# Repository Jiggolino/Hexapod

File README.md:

This project is under construction!

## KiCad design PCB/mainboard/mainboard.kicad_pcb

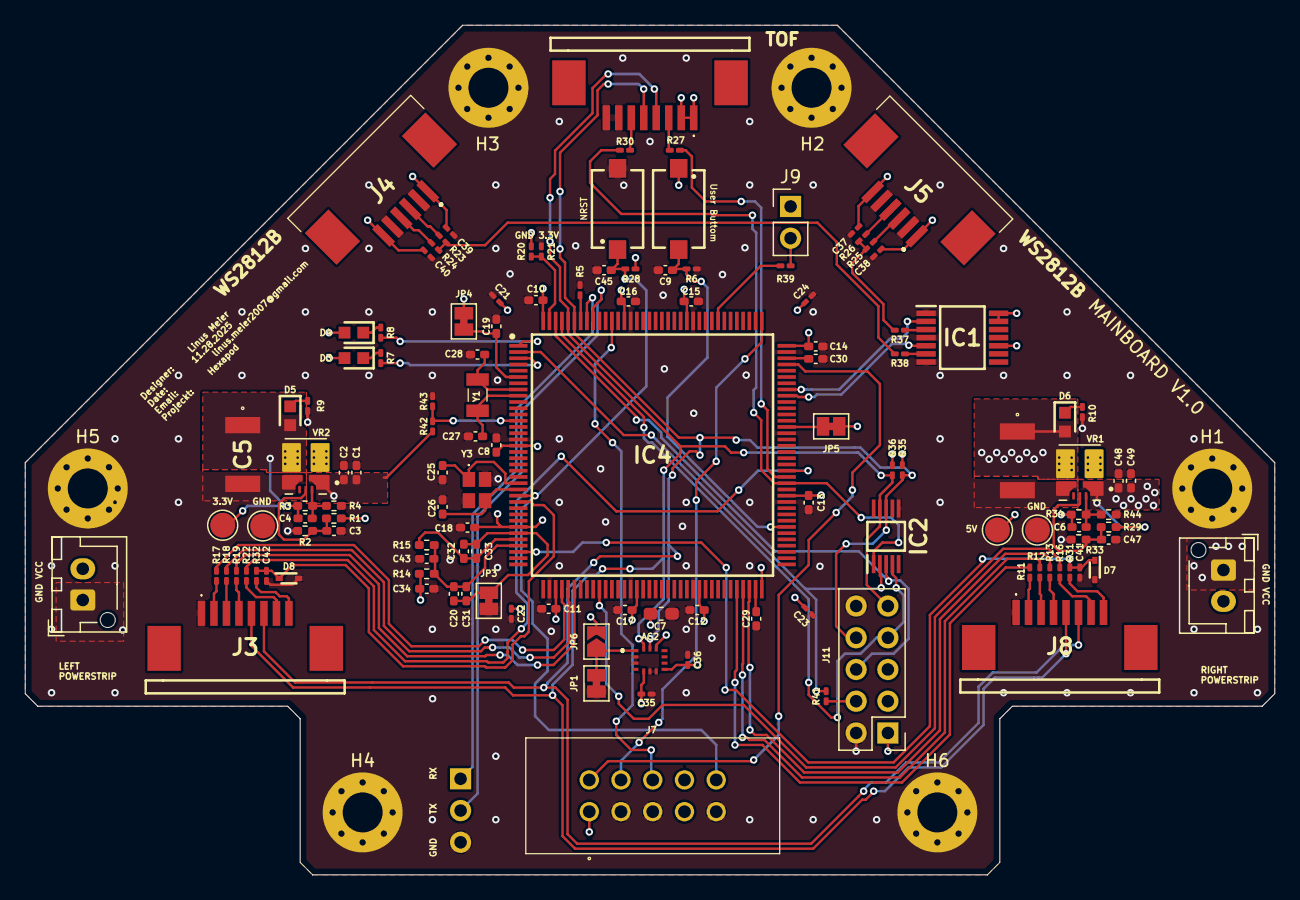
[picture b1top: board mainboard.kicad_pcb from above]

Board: 4 copper layers, 100.0 x 68.0 mm, 133 parts (1 on the bottom side), 78 nets.

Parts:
AC2: LSM6DSOTR; LSM6DS3USTR
C1, C49: 10u; C_0402_1005Metric_Pad0.74x0.62mm_HandSolder
C2, C9, C45, C48: 100n; C_0402_1005Metric_Pad0.74x0.62mm_HandSolder
C3, C47: 10n; C_0402_1005Metric_Pad0.74x0.62mm_HandSolder
C4, C6: 22p; C_0402_1005Metric_Pad0.74x0.62mm_HandSolder
C5, C46: 33u; C4532_Commercial
C7: 4.7uF; C_0603_1608Metric_Pad1.08x0.95mm_HandSolder
C8, C10, C11, C12, C13, C14, C15, C16, C17, C18, C31, C33, C34, C43: 100nF; C_0402_1005Metric_Pad0.74x0.62mm_HandSolder
C19, C20, C32: 1uF; C_0402_1005Metric_Pad0.74x0.62mm_HandSolder
C21, C22, C23, C24, C37, C38, C39, C40: 1u; C_0201_0603Metric_Pad0.64x0.40mm_HandSolder
C25, C26: 6pF; C_0402_1005Metric_Pad0.74x0.62mm_HandSolder
C27, C28: 8pF; C_0402_1005Metric_Pad0.74x0.62mm_HandSolder
C29, C30: 2.2u; C_0402_1005Metric_Pad0.74x0.62mm_HandSolder
C35, C36, C41, C42: 100n; C_0201_0603Metric_Pad0.64x0.40mm_HandSolder
D3: LED_Red; LEDC1608X70N
D4, D5, D6: LED_Geen; LEDC1608X70N
D7, D8: BZT585B3V3T-7; SODFL1608X65N
H1, H2, H3, H4, H5, H6: MountingHole_Pad; MountingHole_3.2mm_M3_Pad_Via
IC1: 74HCT125T14-13; SOP65P640X120-14N
IC2: SP4065-08ATG; SOP50P488X110-10N
IC4: STM32H743ZIT6; QFP50P2200X2200X160-144N
J1: Right Strip Power; JST_XH_B2B-XH-AM_1x02_P2.50mm_Vertical
J2: Left Strip Power; JST_XH_B2B-XH-AM_1x02_P2.50mm_Vertical
J3: Left Strip; 17352658
J4: LED Strip left; 849526
J5: LED Strip right; 849526
J6: Time Of Flight; 17352658
J7: TST-105-01-L-D; TST-105-XX-Y-D
J8: Right Strip; 17352658
J9: LED_CAM; PinHeader_1x02_P2.54mm_Vertical
J10: Uart Connector to pi5; PinSocket_1x03_P2.54mm_Vertical
J11: Conn_02x05_Counter_Clockwise; PinHeader_2x05_P2.54mm_Vertical
JP1, JP3, JP4, JP5: SolderJumper_2_Bridged; SolderJumper-2_P1.3mm_Bridged_Pad1.0x1.5mm
JP6: SolderJumper_2_Open; SolderJumper-2_P1.3mm_Open_TrianglePad1.0x1.5mm
R1, R29: 27.4k; R_0402_1005Metric_Pad0.72x0.64mm_HandSolder
R2, R33: 10k; R_0402_1005Metric_Pad0.72x0.64mm_HandSolder
R3: 220k; R_0402_1005Metric_Pad0.72x0.64mm_HandSolder
R4, R44: 30k; R_0402_1005Metric_Pad0.72x0.64mm_HandSolder
R5, R6, R20, R21, R28, R43: 10k; R_0201_0603Metric_Pad0.64x0.40mm_HandSolder
R7, R8, R9, R39: 100R; R_0201_0603Metric_Pad0.64x0.40mm_HandSolder
R10: 270R; R_0201_0603Metric_Pad0.64x0.40mm_HandSolder
R11, R12, R13, R16, R17, R18, R19, R22, R23, R24, R25, R26, R27, R30, R37, R38, R41: 47R; R_0201_0603Metric_Pad0.64x0.40mm_HandSolder
R14, R15: 0R; R_0402_1005Metric_Pad0.72x0.64mm_HandSolder
R31, R32: 10R; R_0201_0603Metric_Pad0.64x0.40mm_HandSolder
R34: 135k; R_0402_1005Metric_Pad0.72x0.64mm_HandSolder
R35, R36: 4.7k; R_0201_0603Metric_Pad0.64x0.40mm_HandSolder
R42: 100k; R_0201_0603Metric_Pad0.64x0.40mm_HandSolder
S1, S4: 434121025816
TP1, TP2, TP3, TP4: TestPoint; TestPoint_Pad_D2.0mm
VR1, VR2: TPSM863252RDXR; VREG_TPSM863252RDXR
Y1: CM7V-T1A-32.768KHZ-7PF-20PPM-TA-QC; CM7V32768TBQA020
Y3: ECS-250-8-36CKM-TR3; ECS250836CKMTR3

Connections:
+3V3: AC2.5 (VDDIO), AC2.8 (VDD), AC2.12 (CS), C4.1, C5.1, C7.1, C8.1, C10.1, C11.1, C12.1, C13.1, C14.1, C15.1, C16.1, C17.1, C18.1, C21.1, C22.1, C23.1, C24.1, C34.1, C35.1, C36.1, D3.2 (A), D4.2 (A), D5.2 (A), IC4.17 (VDD_1), IC4.30 (VDD_2), IC4.39 (VDD_3), IC4.52 (VDD_4), IC4.62 (VDD_5), IC4.72 (VDD_6), IC4.84 (VDD_7), IC4.108 (VDD_8), IC4.121 (VDD_9), IC4.131 (VDD_10), IC4.144 (VDD_11), J6.1, J6.2, J7.1, J9.1, J11.1, JP4.2 (B), JP5.1 (A), JP6.2 (B), R3.1, R14.1, R20.2, R28.2, R35.1, R36.1, S1.1 (COM), TP3.1, VR2.3 (VOUT)
+5V: C6.1, C37.1, C38.1, C39.1, C40.1, C46.1, D6.2 (A), IC1.10 (3~OE), IC1.13 (4~OE), IC1.14 (VCC), J4.1, J4.6, J5.1, J5.6, J11.5, R34.1, TP1.1, VR1.3 (VOUT)
Battery Voltage: IC4.13 (PF3), R42.1, R43.2
Boot0: IC4.138 (BOOT0), R5.2
DIN Board 1: R23.2, R24.2, R38.1
DIN Board 2: R25.2, R26.2, R37.1
DIN WS2812B Board 1 3.3V: IC1.5 (2A), IC4.100 (PA8)
DIN WS2812B Board 2 3.3V: IC1.2 (1A), IC4.101 (PA9)
GND: AC2.2 (SDX), AC2.3 (SCX), AC2.6 (GND_1), AC2.7 (GND_2), C1.2, C2.2, C3.2, C5.2, C7.2, C8.2, C9.1, C10.2, C11.2, C12.2, C13.2, C14.2, C15.2, C16.2, C17.2, C18.2, C19.2, C21.2, C22.2, C23.2, C24.2, C25.1, C26.2, C27.2, C28.2, C29.2, C30.2, C34.2, C35.2, C36.2, C37.2, C38.2, C39.2, C40.2, C41.2, C42.2, C43.2, C45.1, C46.2, C47.2, C48.2, C49.2, D7.2 (A), D8.2 (A), H1.1, H2.1, H3.1, H4.1, H5.1, H6.1, IC1.1 (1~OE), IC1.4 (2~OE), IC1.7 (GND), IC2.6 (GND), IC4.16 (VSS_1), IC4.38 (VSS_2), IC4.51 (VSS_3), IC4.61 (VSS_4), IC4.83 (VSS_5), IC4.94 (VSS_6), IC4.107 (VSS_7), IC4.120 (VSS_8), IC4.130 (VSS_9), J1.1, J2.1, J3.1, J4.2, J4.5, J5.2, J5.5, J6.7, J6.8, J7.3, J7.5, J7.9, J8.1, J10.3, J11.2, J11.10, JP1.1 (A), JP3.1 (A), R2.2, R4.2, R5.1, R6.1, R9.2, R10.2, R21.2, R33.2, R43.1, R44.2, S4.2 (NO), TP2.1, TP4.1, VR1.4 (PGND), VR2.4 (PGND), Y3.2 (GND_1), Y3.4 (GND_2)
GNDA: C20.2, C31.2, C32.2, C33.2, IC4.31 (VSSA), JP3.2 (B)
GPIO 1: IC4.87 (PG2), R27.2
GPIO Expansion 1: IC2.4 (I/O_4), IC4.141 (PE0), J11.7
GPIO Expansion 2: IC2.3 (I/O_3), IC4.142 (PE1), J11.6
GPIO Expansion 3: IC2.2 (I/O_2), IC4.2 (PE3), R41.1
LED_CAM: IC4.116 (PD2), R39.2
NRST: C45.2, IC4.25 (NRST), J7.10, R28.1, S4.1 (COM)
unnamed: AC2.1 (SDO/SA0), JP1.2 (B), JP6.1 (A)
unnamed: D3.1 (K), R7.1
unnamed: D4.1 (K), R8.1
unnamed: D5.1 (K), R9.1
unnamed: D6.1 (K), R10.1
unnamed: IC1.3 (1Y), R37.2
unnamed: IC1.6 (2Y), R38.2
unnamed: J3.2, R17.1
unnamed: J3.3, R18.1
unnamed: J3.4, R19.1
unnamed: J3.7, R22.1
unnamed: J3.8, R32.1
unnamed: J4.3, R23.1
unnamed: J4.4, R24.1
unnamed: J5.3, R25.1
unnamed: J5.4, R26.1
unnamed: J6.3, R27.1
unnamed: J6.6, R30.1
unnamed: J8.2, R11.1
unnamed: J8.3, R12.1
unnamed: J8.4, R13.1
unnamed: J8.7, R16.1
unnamed: J8.8, R31.1
unnamed: J9.2, R39.1
unnamed: J11.4, R41.2
unnamed: C47.1, R29.2, R33.1, VR1.6 (EN)
unnamed: C6.2, R34.2, R44.1, VR1.7 (FB)
unnamed: C3.1, R1.2, R2.1, VR2.6 (EN)
unnamed: C4.2, R3.2, R4.1, VR2.7 (FB)
PC14-OSC32_IN: C28.1, IC4.8 (PC14-OSC32_IN), Y1.1
PC15-OSC32_OUT: C27.1, IC4.9 (PC15-OSC32_OUT), Y1.2
PDR_ON: IC4.143 (PDR_ON), R20.1, R21.1
PE2 (LED): IC4.1 (PE2), R8.2
PE4 (LED): IC4.3 (PE4), R7.2
PH0-OSC_IN: C25.2, IC4.23 (PH0-OSC_IN), Y3.1 (IN/OUT)
PH1-OSC_OUT: C26.1, IC4.24 (PH1-OSC_OUT), Y3.3 (OUT/IN)
RX: IC4.137 (PB7), J10.1
SCL: AC2.13 (SCL), IC2.8 (I/O_6), IC4.139 (PB8), J3.6, J6.5, J8.6, J11.8, R35.2
SDA: AC2.14 (SDA), IC2.9 (I/O_7), IC4.140 (PB9), J3.5, J6.4, J8.5, J11.9, R36.2
SWCLK: IC4.109 (PA14), J7.4
SWDIO: IC4.105 (PA13), J7.2
SWO: IC4.133 (PB3), J7.6
TX: IC4.136 (PB6), J10.2
User Button: C9.2, IC4.79 (PD10), R6.2, S1.2 (NO)
VBAT: C19.1, IC4.6 (VBAT), JP4.1 (A)
VCAP_1: C29.1, IC4.71 (VCAP_1)
VCAP_2: C30.1, IC4.106 (VCAP_2)
VCC: C1.1, C2.1, C48.1, C49.1, J1.2, J2.2, J11.3, R1.1, R29.1, R42.2, VR1.1 (VIN), VR2.1 (VIN)
VDD33_USB: IC4.95 (VDD33USB), JP5.2 (B)
VDDA: C20.1, C31.1, C43.1, IC4.33 (VDDA), R14.2, R15.1
VREFP: C32.1, C33.1, IC4.32 (VREF+), R15.2
XSHUT: IC2.1 (I/O_1), IC4.86 (PD15), R30.2
left_A0: IC4.42 (PA6), R19.2
left_A1: IC4.41 (PA5), R18.2
left_A2: IC4.40 (PA4), R17.2
left_ADC INPUT: C42.1, D8.1 (K), IC4.26 (PC0), R32.2
left_¬EN: IC4.88 (PG3), R22.2
right_A0: IC4.70 (PB11), R13.2
right_A1: IC4.69 (PB10), R12.2
right_A2: IC4.68 (PE15), R11.2
right_ADC INPUT: C41.1, D7.1 (K), IC4.34 (PA0), R31.2
right_¬EN: IC4.46 (PB0), R16.2

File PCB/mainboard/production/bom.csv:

Designator,Footprint,Quantity,Value,LCSC Part #
AC2,LSM6DS3USTR,1,LSM6DSOTR,
"C1, C49",0402,2,10u,
"C10, C11, C12, C13, C14, C15, C16, C17, C18, C31, C33, C34, C43, C8",0402,14,100nF,
"C19, C20, C32",0402,3,1uF,
"C2, C45, C48, C9",0402,4,100n,
"C21, C22, C23, C24, C37, C38, C39, C40",0201,8,1u,
"C25, C26",0402,2,6pF,
"C27, C28",0402,2,8pF,
"C29, C30",0402,2,2.2u,
"C3, C47",0402,2,10n,
"C35, C36, C41, C42",0201,4,100n,
"C4, C6",0402,2,22p,
"C46, C5",C4532_Commercial,2,33u,
C7,0603,1,4.7uF,
D3,LEDC1608X70N,1,LED_Red,
"D4, D5, D6",LEDC1608X70N,3,LED_Geen,
"D7, D8",SODFL1608X65N,2,BZT585B3V3T-7,
IC1,SOP65P640X120-14N,1,74HCT125T14-13,
IC2,SOP50P488X110-10N,1,SP4065-08ATG,
IC4,QFP50P2200X2200X160-144N,1,STM32H743ZIT6,
J1,JST_XH_B2B-XH-AM_1x02_P2.50mm_Vertical,1,Right Strip Power,
J10,PinSocket_1x03_P2.54mm_Vertical,1,Uart Connector to pi5,
J11,PinHeader_2x05_P2.54mm_Vertical,1,Conn_02x05_Counter_Clockwise,
J2,JST_XH_B2B-XH-AM_1x02_P2.50mm_Vertical,1,Left Strip Power,
J3,17352658,1,Left Strip,
J4,849526,1,LED Strip left,
J5,849526,1,LED Strip right,
J6,17352658,1,Time Of Flight,
J7,TST-105-XX-Y-D,1,TST-105-01-L-D,
J8,17352658,1,Right Strip,
J9,PinHeader_1x02_P2.54mm_Vertical,1,LED_CAM,
"R1, R29",0402,2,27.4k,
R10,0201,1,270R,
"R11, R12, R13, R16, R17, R18, R19, R22, R23, R24, R25, R26, R27, R30, R37, R38, R41",0201,17,47R,
"R14, R15",0402,2,0R,
"R2, R33",0402,2,10k,
"R20, R21, R28, R43, R5, R6",0201,6,10k,
R3,0402,1,220k,
"R31, R32",0201,2,10R,
R34,0402,1,135k,
"R35, R36",0201,2,4.7k,
"R39, R7, R8, R9",0201,4,100R,
"R4, R44",0402,2,30k,
R42,0201,1,100k,
"S1, S4",434121025816,2,434121025816,
"TP1, TP2, TP3, TP4",TestPoint_Pad_D2.0mm,4,TestPoint,
"VR1, VR2",VREG_TPSM863252RDXR,2,TPSM863252RDXR,
Y1,CM7V32768TBQA020,1,CM7V-T1A-32.768KHZ-7PF-20PPM-TA-QC,
Y3,ECS250836CKMTR3,1,ECS-250-8-36CKM-TR3,

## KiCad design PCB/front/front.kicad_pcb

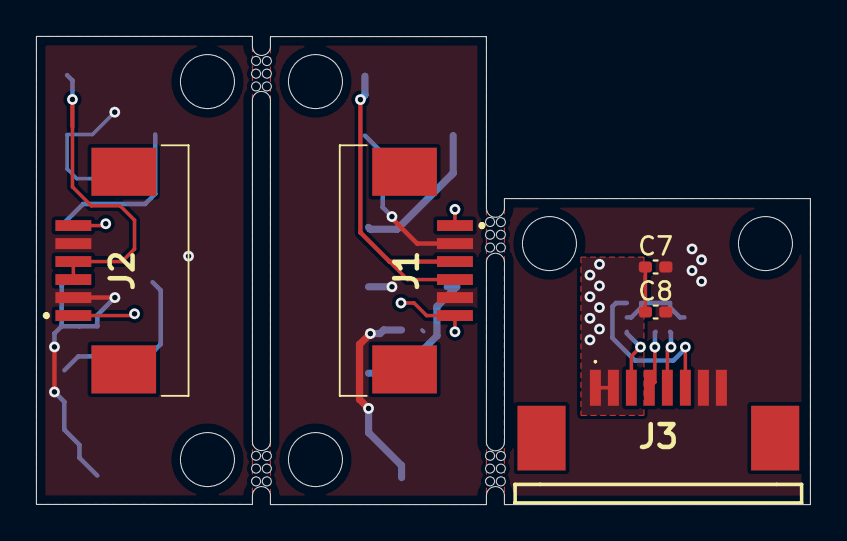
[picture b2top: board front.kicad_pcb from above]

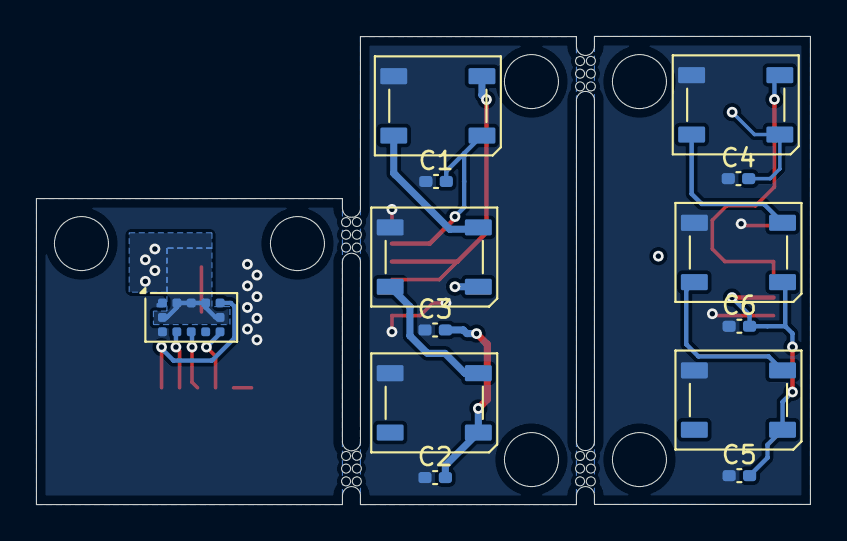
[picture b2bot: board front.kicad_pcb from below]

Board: 2 copper layers, 43.0 x 26.0 mm, 22 parts (13 on the bottom side), 16 nets.

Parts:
C1, C2, C3, C4, C5, C6, C7, C8: 100n; C_0402_1005Metric_Pad0.74x0.62mm_HandSolder
D1, D2, D3, D4, D5, D6: WS2812B; LED_WS2812B_PLCC4_5.0x5.0mm_P3.2mm
J1, J2: Conn_01x06_Pin; 849526
J3: Conn_01x08_Pin; 17352658
TP1, TP2, TP3, TP4: TestPoint; mouse-bite-1mm-3mm
U1: VL53L1CXV0FY1; ST_VL53L1x

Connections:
3.3V: C7.1, C8.1, J3.1, J3.2, U1.1 (AVDDVCSEL), U1.11 (AVDD)
5V Board 1: C1.1, C2.1, C3.1, D1.1 (VDD), D2.1 (VDD), D3.1 (VDD), J1.1, J1.6
5V Board 2: C4.1, C5.1, C6.1, D4.1 (VDD), D5.1 (VDD), D6.1 (VDD), J2.1, J2.6
DIN Board 1: D1.4 (DIN), J1.3, J1.4
DIN Board 2: D4.4 (DIN), J2.3, J2.4
GND: C7.2, C8.2, J3.7, J3.8, U1.2 (AVSSVCSEL), U1.3 (GND), U1.4 (GND), U1.6 (GND), U1.12 (GND)
GND Board 1: C1.2, C2.2, C3.2, D1.3 (VSS), D2.3 (VSS), D3.3 (VSS), J1.2, J1.5
GND Board 2: C4.2, C5.2, C6.2, D4.3 (VSS), D5.3 (VSS), D6.3 (VSS), J2.2, J2.5
GPIO 1: J3.3, U1.7 (GPIO1)
unnamed: D1.2 (DOUT), D2.4 (DIN)
unnamed: D2.2 (DOUT), D3.4 (DIN)
unnamed: D4.2 (DOUT), D5.4 (DIN)
unnamed: D5.2 (DOUT), D6.4 (DIN)
SCL: J3.5, U1.10 (SCL)
SDA: J3.4, U1.9 (SDA)
XSHUT: J3.6, U1.5 (XSHUT)

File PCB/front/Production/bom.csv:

Designator,Footprint,Quantity,Value,LCSC Part #
"C1, C2, C3, C4, C5, C6, C7, C8",0402,8,100n,
"D1, D2, D3, D4, D5, D6",LED_WS2812B_PLCC4_5.0x5.0mm_P3.2mm,6,WS2812B,
"J1, J2",849526,2,Conn_01x06_Pin,
J3,17352658,1,Conn_01x08_Pin,
"TP1, TP2, TP3, TP4",mouse-bite-1mm-3mm,4,TestPoint,
U1,ST_VL53L1x,1,VL53L1CXV0FY1,

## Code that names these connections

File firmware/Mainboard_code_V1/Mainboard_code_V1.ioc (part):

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Mcu.Name=STM32H743ZITx
Mcu.Package=LQFP144
Mcu.UserName=STM32H743ZITx
PA0.GPIOParameters=GPIO_Label
PA0.GPIO_Label=Right_Current_Sense
PA0.Mode=IN16-Single-Ended
PA0.Signal=ADC1_INP16
PA13\ (JTMS/SWDIO).Signal=DEBUG_JTMS-SWDIO
PA14\ (JTCK/SWCLK).Signal=DEBUG_JTCK-SWCLK
PA4.GPIOParameters=GPIO_Label
PA4.GPIO_Label=Left_A2
PA4.Signal=GPIO_Output
PA5.GPIOParameters=GPIO_Label
PA5.GPIO_Label=Left_A1
PA5.Signal=GPIO_Output
PA6.GPIOParameters=GPIO_Label
PA6.GPIO_Label=Left_A0
PA6.Signal=GPIO_Output
PA8.GPIOParameters=GPIO_Label
PA8.GPIO_Label=DIN_WS2812B_1
PA8.Signal=S_TIM1_CH1
PA9.GPIOParameters=GPIO_Label
PA9.GPIO_Label=DIN_WS2812B_2
PA9.Signal=S_TIM1_CH2
PB0.GPIOParameters=GPIO_Label
PB0.GPIO_Label=Right_Enable
PB0.Signal=GPIO_Output
PB10.GPIOParameters=GPIO_Label
PB10.GPIO_Label=Right_A1
PB10.Signal=GPIO_Output
PB11.GPIOParameters=GPIO_Label
PB11.GPIO_Label=Right_A0
PB11.Signal=GPIO_Output
PB3\ (JTDO/TRACESWO).Signal=DEBUG_JTDO-SWO
PB6.GPIOParameters=GPIO_Speed,GPIO_PuPd,GPIO_Label
PB6.GPIO_Label=UART_TX_SERIAL
PB6.GPIO_PuPd=GPIO_NOPULL
PB6.GPIO_Speed=GPIO_SPEED_FREQ_VERY_HIGH
PB6.Mode=Asynchronous
PB6.Signal=USART1_TX
PB7.GPIOParameters=GPIO_Speed,GPIO_Label
PB7.GPIO_Label=UART_RX_SERIAL
PB7.GPIO_Speed=GPIO_SPEED_FREQ_VERY_HIGH
PB7.Mode=Asynchronous
PB7.Signal=USART1_RX
PB8.GPIOParameters=GPIO_Speed
PB8.GPIO_Speed=GPIO_SPEED_FREQ_VERY_HIGH
PB8.Mode=I2C
PB8.Signal=I2C1_SCL
PB9.GPIOParameters=GPIO_Speed
PB9.GPIO_Speed=GPIO_SPEED_FREQ_VERY_HIGH
PB9.Mode=I2C
PB9.Signal=I2C1_SDA
PC0.GPIOParameters=GPIO_Label
PC0.GPIO_Label=Left_Current_Sense
PC0.Signal=ADCx_INP10
PD10.GPIOParameters=GPIO_Label
PD10.GPIO_Label=User_Button
PD10.Signal=GPIO_Input
PD15.GPIOParameters=GPIO_Label
PD15.GPIO_Label=XSHUT
PD15.Signal=GPIO_Output
PD2.GPIOParameters=GPIO_Label
PD2.GPIO_Label=LED_CAM
PD2.Signal=GPIO_Output
PE15.GPIOParameters=GPIO_Label
PE15.GPIO_Label=Right_A2
PE15.Signal=GPIO_Output
PE2.GPIOParameters=GPIO_Label
PE2.GPIO_Label=LED_GREEN
PE2.Signal=GPIO_Output
PE4.GPIOParameters=GPIO_Label
PE4.GPIO_Label=LED_RED
PE4.Signal=GPIO_Output
PF3.GPIOParameters=GPIO_Label
PF3.GPIO_Label=Battery_Voltage
PF3.Mode=IN5-Single-Ended
PF3.Signal=ADC3_INP5
PG2.GPIOParameters=GPIO_PuPd,GPIO_Label
PG2.GPIO_Label=GPIO_1_TOF
PG2.GPIO_PuPd=GPIO_PULLUP
PG2.Signal=GPIO_Input
PG3.GPIOParameters=GPIO_Label
PG3.GPIO_Label=Left_Enable
PG3.Signal=GPIO_Output
RCC.SYSCLKFreq_VALUE=32000000
board=custom

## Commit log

2025-09-12 Initial commit with LFS
2025-09-16 requirements
2025-09-17 Anforderungen und zeitplan
2025-09-19 Projektdokumentation
2025-09-22 work log excel update
2025-09-23 3D Print files
2025-09-26 sliced and Prined 3D files
2025-09-29 cad Changes
2025-09-30 Leg V2 step/stl fies
2025-09-30 Doku
2025-10-02 weekly upload
2025-11-03 random upload
2025-11-11 Stripe PCB's
2025-11-17 STM32 Mainboard requirements for Programing and Power
2025-11-20 upgrades to STM32 Board
2025-11-28 Made the Mainboard BCP Part Layout
2025-12-02 Stop tracking renders folder & final Powerstrip and Mainboard PCB
2025-12-18 random
2026-01-07 Doku + new License
2026-01-07 Doku and cleaning up
2026-01-12 random save
2026-02-19 svaing project
2026-02-26 radnom upload
2026-03-12 timeplan upload
2026-03-12 Preperation 2 Semester
2026-03-16 servo numbers
2026-03-23 URFD
2026-04-13 Kicad PCBS 10.0 and git errors resolve
2026-04-13 Kicad 10.0 integration and PCB Coruption resolved
2026-05-18 Revise LICENSE file with updated terms
    Updated the license terms and conditions, clarifying prohibited uses and permission requests.
